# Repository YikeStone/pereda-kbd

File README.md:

# Pereda

Pereda is a custom wireless mechanical keyboard designed for **Kailh Choc V1** switches.

It has **46 keys**, aggressive **column stagger**, and **column splay**. The key positions are designed around my finger length and natural finger-joint movement rather than a conventional keyboard layout.

Finished Product:

## Hardware

* Kailh Choc V1 switches
* Seeed Studio XIAO nRF52840
* Wireless
* 46 keys
* Aggressive column stagger and column splay
* Reversible PCB
* 301230 LiPo battery, 120 mAh
* Magnetic USB-C connector for charging
* Custom ergonomic key layout

## Build Details

* **Top plate:** 1 mm laser-cut aluminum, spray-painted black
* **PCB:** Black solder mask
* **Keyboard height:** ~1.5 cm from the table surface
* **Feet:** 8 × 3 mm silicone dots to prevent sliding

## Assembly

After soldering the XIAO nRF52840 module to the PCB, a battery pad on the underside of the XIAO remains accessible through the cutout in the PCB.

Solder the exposed battery pad on the XIAO to the corresponding battery pad on the PCB using a short wire.

The PCB is reversible, allowing the same PCB design to be used for either side.

## Firmware

Pereda uses **ZMK firmware**.

[Pereda ZMK Configuration](https://github.com/YikeStone/pereda-zmk)

## Manufacturing

Ready-to-manufacture files are available under:

`manufacturing/v0.2/`

The BOM quantities are for **one PCB/half**.

## Repository

* `common/` — custom symbols, footprints, and 3D models
* `images/` — project images
* `manufacturing/` — BOM, fabrication files, DXF, and CAD
* `*.kicad_*` — KiCad source files

## Status

**v0.2 — functional prototype.**

## Acknowledgements

Inspired by the [Corne keyboard](https://github.com/foostan/crkbd) by foostan.

## License

See `LICENSE`.

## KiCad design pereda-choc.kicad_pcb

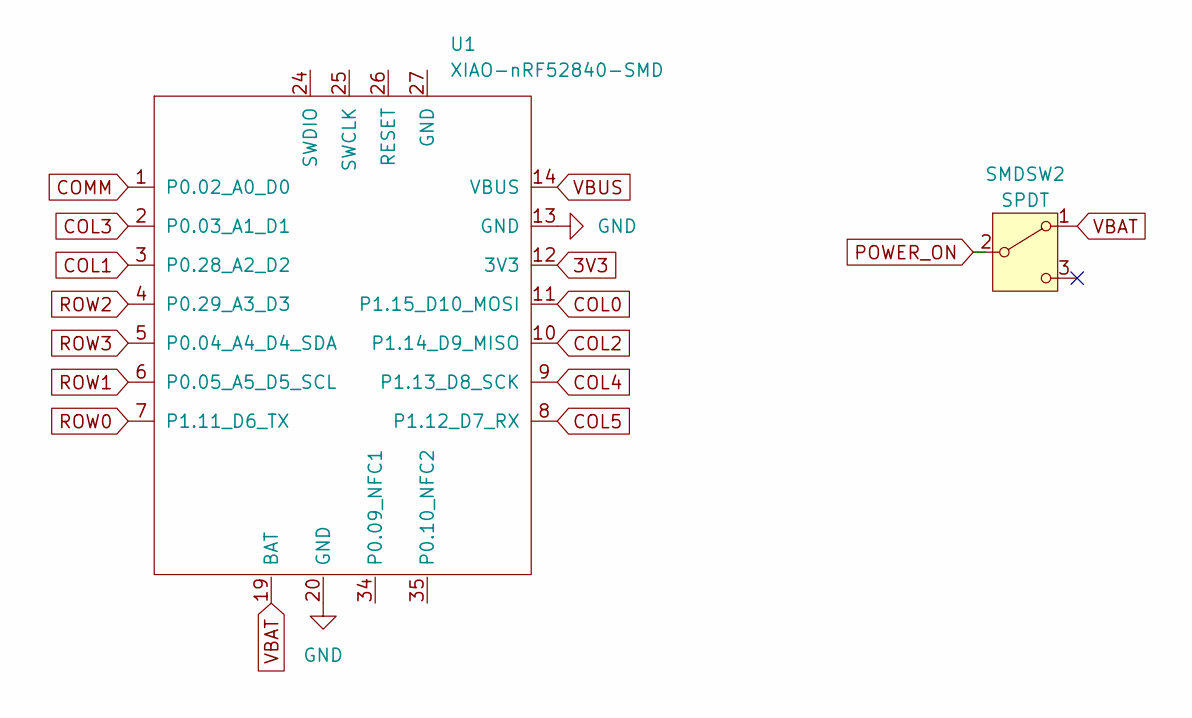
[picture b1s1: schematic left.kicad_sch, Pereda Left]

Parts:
SMDSW2: SPDT; SW_SPDT_PCM12; MPN PCM12SMTBR; JLCPCB Part # C455280
U1: XIAO-nRF52840-SMD; XIAO-nRF52840-SMD-kbd; MPN 101991463

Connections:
3V3: U1.12 (3V3); also elsewhere on the board
COL0: U1.11 (P1.15_D10_MOSI); also elsewhere on the board
COL1: U1.3 (P0.28_A2_D2); also elsewhere on the board
COL2: U1.10 (P1.14_D9_MISO); also elsewhere on the board
COL3: U1.2 (P0.03_A1_D1); also elsewhere on the board
COL4: U1.9 (P1.13_D8_SCK); also elsewhere on the board
COL5: U1.8 (P1.12_D7_RX); also elsewhere on the board
COMM: U1.1 (P0.02_A0_D0); also elsewhere on the board
GND: U1.13 (GND), U1.20 (GND); also elsewhere on the board
POWER_ON: SMDSW2.2 (B); also elsewhere on the board
ROW0: U1.7 (P1.11_D6_TX); also elsewhere on the board
ROW1: U1.6 (P0.05_A5_D5_SCL); also elsewhere on the board
ROW2: U1.4 (P0.29_A3_D3); also elsewhere on the board
ROW3: U1.5 (P0.04_A4_D4_SDA); also elsewhere on the board
VBAT: SMDSW2.1 (A), U1.19 (BAT); also elsewhere on the board
VBUS: U1.14 (VBUS); also elsewhere on the board

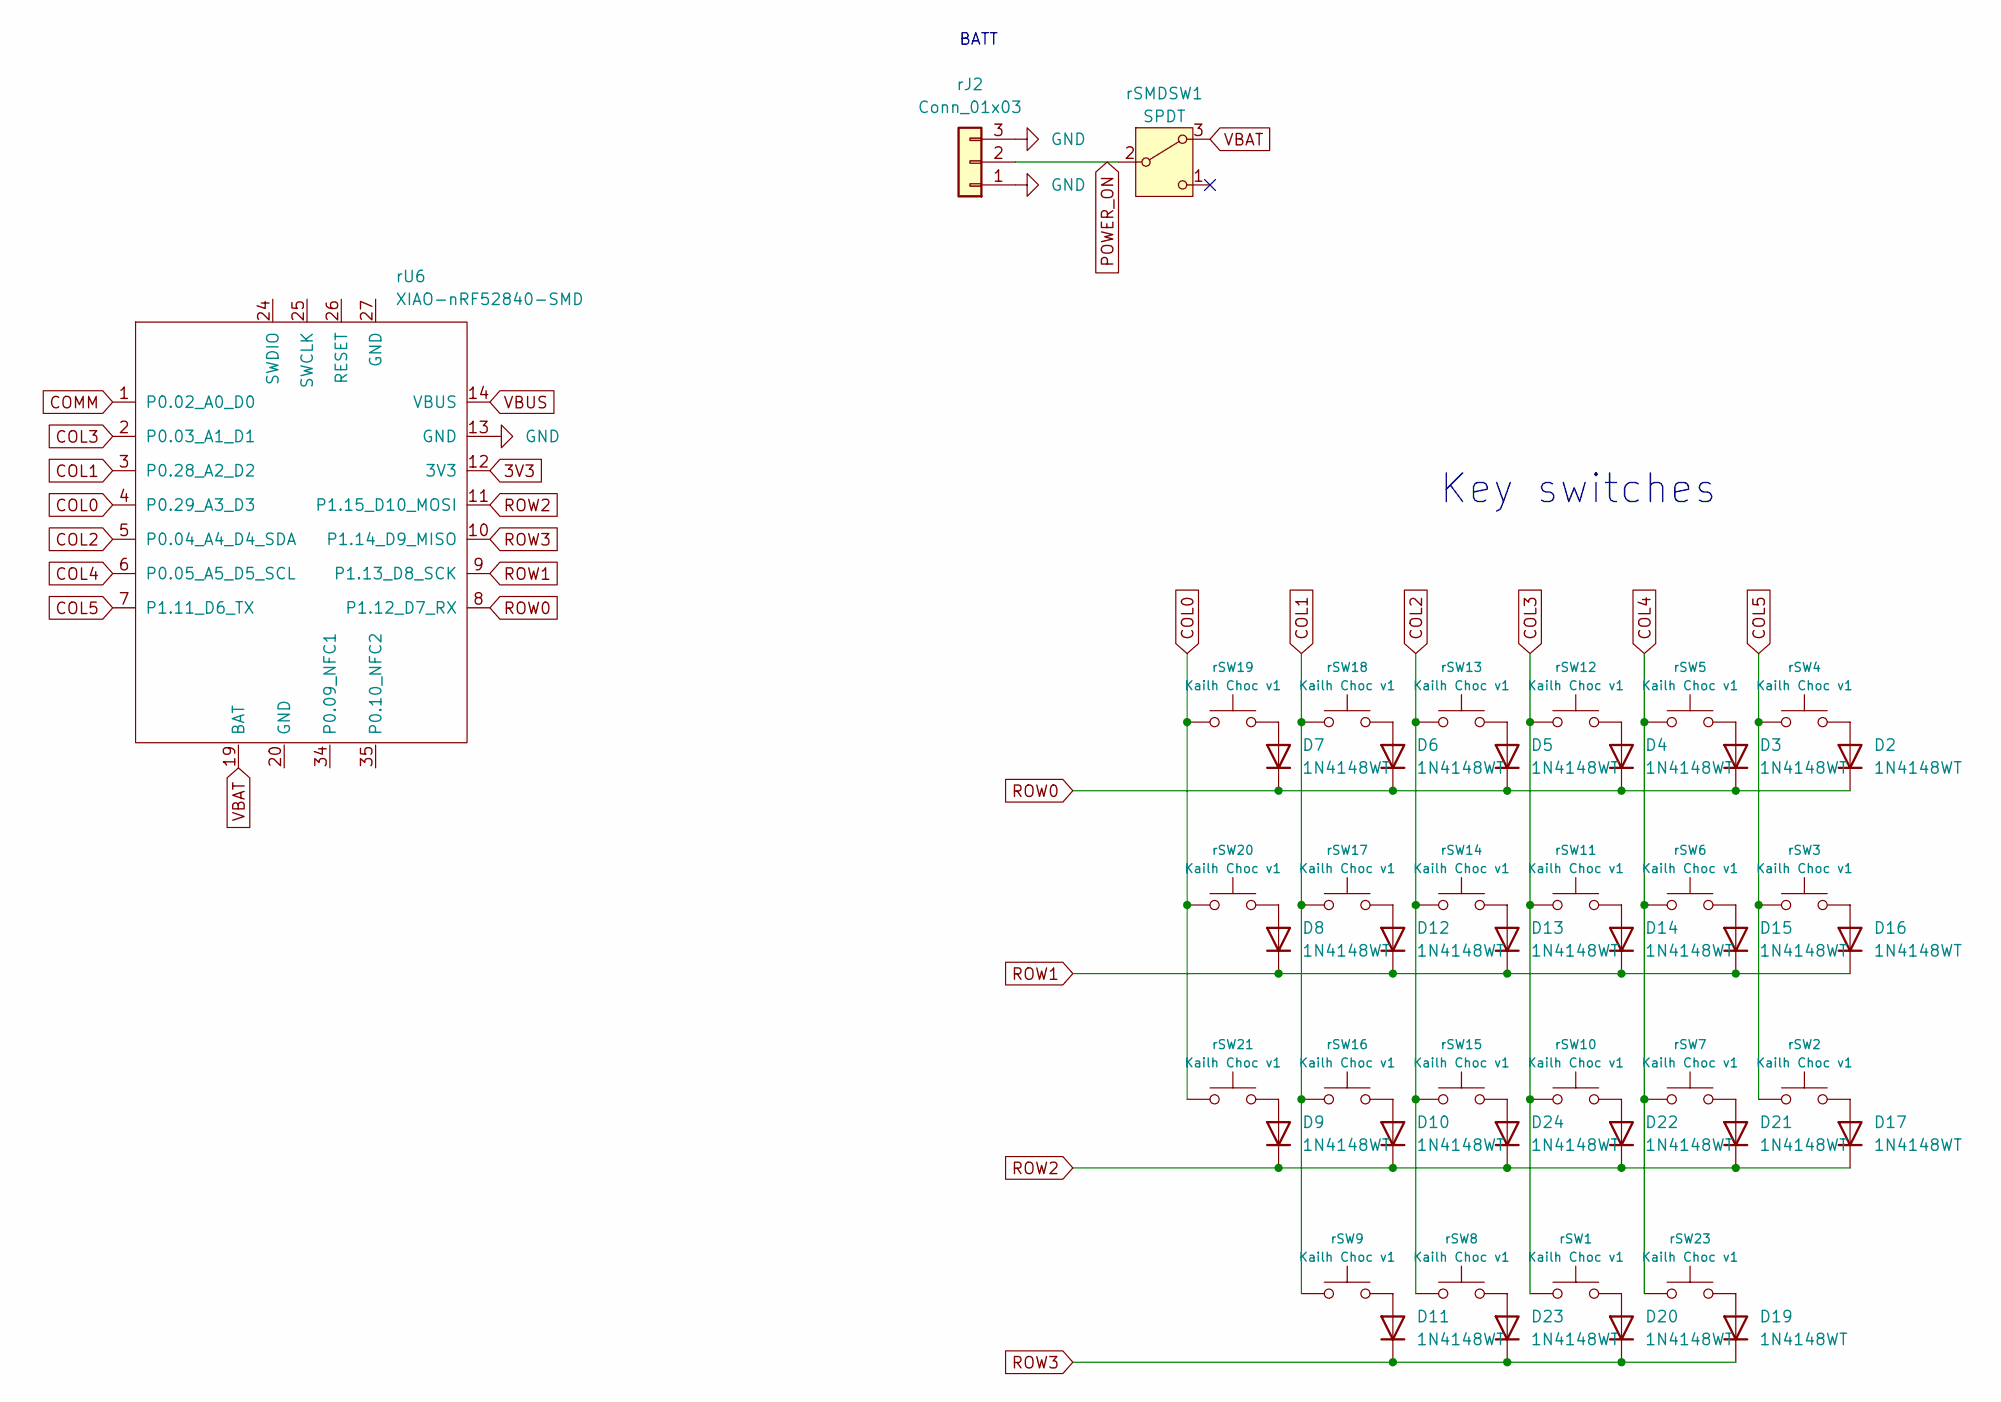
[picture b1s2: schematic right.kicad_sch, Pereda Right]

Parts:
D2, D3, D4, D5, D6, D7, D8, D9, D10, D11, D12, D13, D14, D15, D16, D17, D19, D20, D21, D22, D23, D24: 1N4148WT; D_SOD-123-rev; MPN 1N4148W
rJ2: Conn_01x03; PinHeader_1x03_P2.54mm_Horizontal; MPN M50-3930342
rSMDSW1: SPDT; SW_SPDT_PCM12; MPN PCM12SMTBR; JLCPCB Part # C455280
rSW1: Kailh Choc v1; Kailh_socket_PG1350_reversible_1.25u; MPN 5118
rSW2, rSW3, rSW4, rSW5, rSW6, rSW7, rSW8, rSW9, rSW10, rSW11, rSW12, rSW13, rSW14, rSW15, rSW16, rSW17, rSW18, rSW19, rSW20, rSW21, rSW23: Kailh Choc v1; Kailh_socket_PG1350_reversible_1u; MPN 5118
rU6: XIAO-nRF52840-SMD; XIAO-nRF52840-SMD-kbd; MPN 101991463

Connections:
3V3: rU6.12 (3V3); also elsewhere on the board
COL0: rSW19.1, rSW20.1, rSW21.1, rU6.4 (P0.29_A3_D3); also elsewhere on the board
COL1: rSW9.1, rSW16.1, rSW17.1, rSW18.1, rU6.3 (P0.28_A2_D2); also elsewhere on the board
COL2: rSW8.1, rSW13.1, rSW14.1, rSW15.1, rU6.5 (P0.04_A4_D4_SDA); also elsewhere on the board
COL3: rSW1.1, rSW10.1, rSW11.1, rSW12.1, rU6.2 (P0.03_A1_D1); also elsewhere on the board
COL4: rSW5.1, rSW6.1, rSW7.1, rSW23.1, rU6.6 (P0.05_A5_D5_SCL); also elsewhere on the board
COL5: rSW2.1, rSW3.1, rSW4.1, rU6.7 (P1.11_D6_TX); also elsewhere on the board
COMM: rU6.1 (P0.02_A0_D0); also elsewhere on the board
GND: rJ2.1, rJ2.3, rU6.13 (GND); also elsewhere on the board
unnamed: D2.2 (A), rSW4.2
unnamed: D3.2 (A), rSW5.2
unnamed: D4.2 (A), rSW12.2
unnamed: D5.2 (A), rSW13.2
unnamed: D6.2 (A), rSW18.2
unnamed: D7.2 (A), rSW19.2
unnamed: D8.2 (A), rSW20.2
unnamed: D9.2 (A), rSW21.2
unnamed: D10.2 (A), rSW16.2
unnamed: D11.2 (A), rSW9.2
unnamed: D12.2 (A), rSW17.2
unnamed: D13.2 (A), rSW14.2
unnamed: D14.2 (A), rSW11.2
unnamed: D15.2 (A), rSW6.2
unnamed: D16.2 (A), rSW3.2
unnamed: D17.2 (A), rSW2.2
unnamed: D19.2 (A), rSW23.2
unnamed: D20.2 (A), rSW1.2
unnamed: D21.2 (A), rSW7.2
unnamed: D22.2 (A), rSW10.2
unnamed: D23.2 (A), rSW8.2
unnamed: D24.2 (A), rSW15.2
POWER_ON: rJ2.2, rSMDSW1.2 (B); also elsewhere on the board
ROW0: D2.1 (K), D3.1 (K), D4.1 (K), D5.1 (K), D6.1 (K), D7.1 (K), rU6.8 (P1.12_D7_RX); also elsewhere on the board
ROW1: D8.1 (K), D12.1 (K), D13.1 (K), D14.1 (K), D15.1 (K), D16.1 (K), rU6.9 (P1.13_D8_SCK); also elsewhere on the board
ROW2: D9.1 (K), D10.1 (K), D17.1 (K), D21.1 (K), D22.1 (K), D24.1 (K), rU6.11 (P1.15_D10_MOSI); also elsewhere on the board
ROW3: D11.1 (K), D19.1 (K), D20.1 (K), D23.1 (K), rU6.10 (P1.14_D9_MISO); also elsewhere on the board
VBAT: rSMDSW1.3 (A), rU6.19 (BAT); also elsewhere on the board
VBUS: rU6.14 (VBUS); also elsewhere on the board

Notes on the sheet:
BATT
Key switches

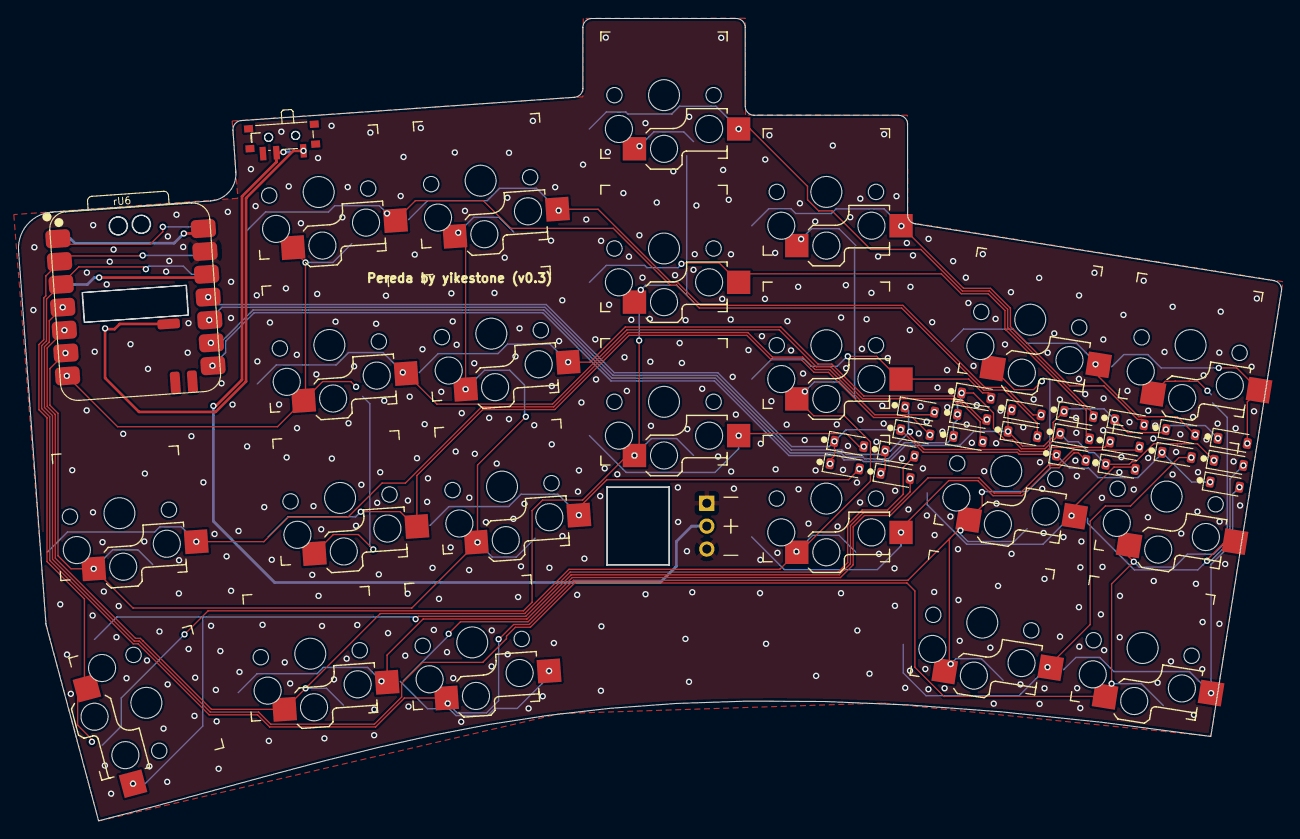
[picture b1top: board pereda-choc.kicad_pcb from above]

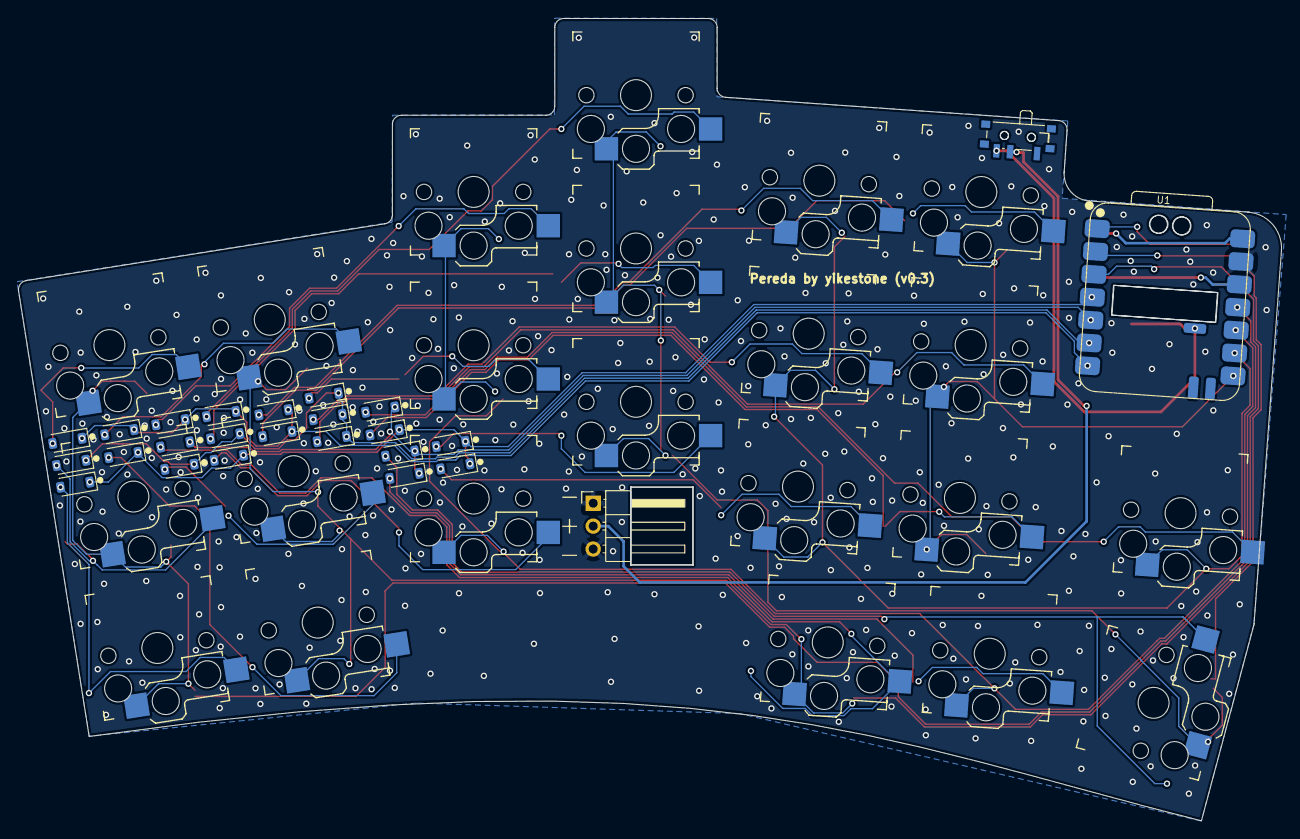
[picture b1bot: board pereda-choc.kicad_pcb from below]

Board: 2 copper layers, 140.0 x 89.0 mm, 49 parts (25 on the bottom side), 38 nets.

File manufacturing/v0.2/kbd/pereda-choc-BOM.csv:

Reference,Qty,Value,Exclude from BOM,Exclude from Board,MPN,Manufacturer
"rSMDSW1,SMDSW2",1,SPDT,,,PCM12SMTBR,
"rSW2,rSW3,rSW4,rSW5,rSW6,rSW7,rSW8,rSW9,rSW10,rSW11,rSW12,rSW13,rSW14,rSW15,rSW16,rSW17,rSW18,rSW19,rSW20,rSW21,rSW22,rSW23",22,Kailh Choc v1,,,5118,
rSW1,1,Kailh Choc v1,,,5118,
"rU6,U1",1,XIAO-nRF52840-SMD,,,101991463,"Seeed Technology Co., Ltd"
"D2,D3,D4,D5,D6,D7,D8,D9,D10,D11,D12,D13,D14,D15,D16,D17,D18,D19,D20,D21,D22,D23,D24",23,1N4148WT,,,1N4148W,Diotec Semiconductor
